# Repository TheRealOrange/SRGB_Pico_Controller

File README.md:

# RPi Pico Signal RGB Controller

This is a simple addressable RGB LED controller (WS2812 LEDs) based on the [Raspberry Pi Pico](https://www.raspberrypi.com/products/raspberry-pi-pico/), and compatible with the PC component RGB lighting software known as [Signal RGB](https://www.signalrgb.com/).  This controller features 8 independent addressable RGB LED outputs, each with filtering capacitors and a resistor on the data line per the recommended specifications. Each LED channel is also driven by the Pico through a level-shifter, providing full 5V to the data line. To supply 5V to the controller, there are two pads where the user can choose to solder a Molex, SATA power, or other 5V power source.

In case anyone wants to use this design, the KiCAD project files are in the folder `srgb_pico`, and the symbol fields list both LCSC and DigiKey part numbers.

The number of LEDs on each channel is configurable via the online configurator available at [SRGBmods](https://srgbmods.net/). The controller made possible by, and relies on the code provided by [SRGBmods](https://srgbmods.net/). I am not the author of the code which is meant to run on this controller.

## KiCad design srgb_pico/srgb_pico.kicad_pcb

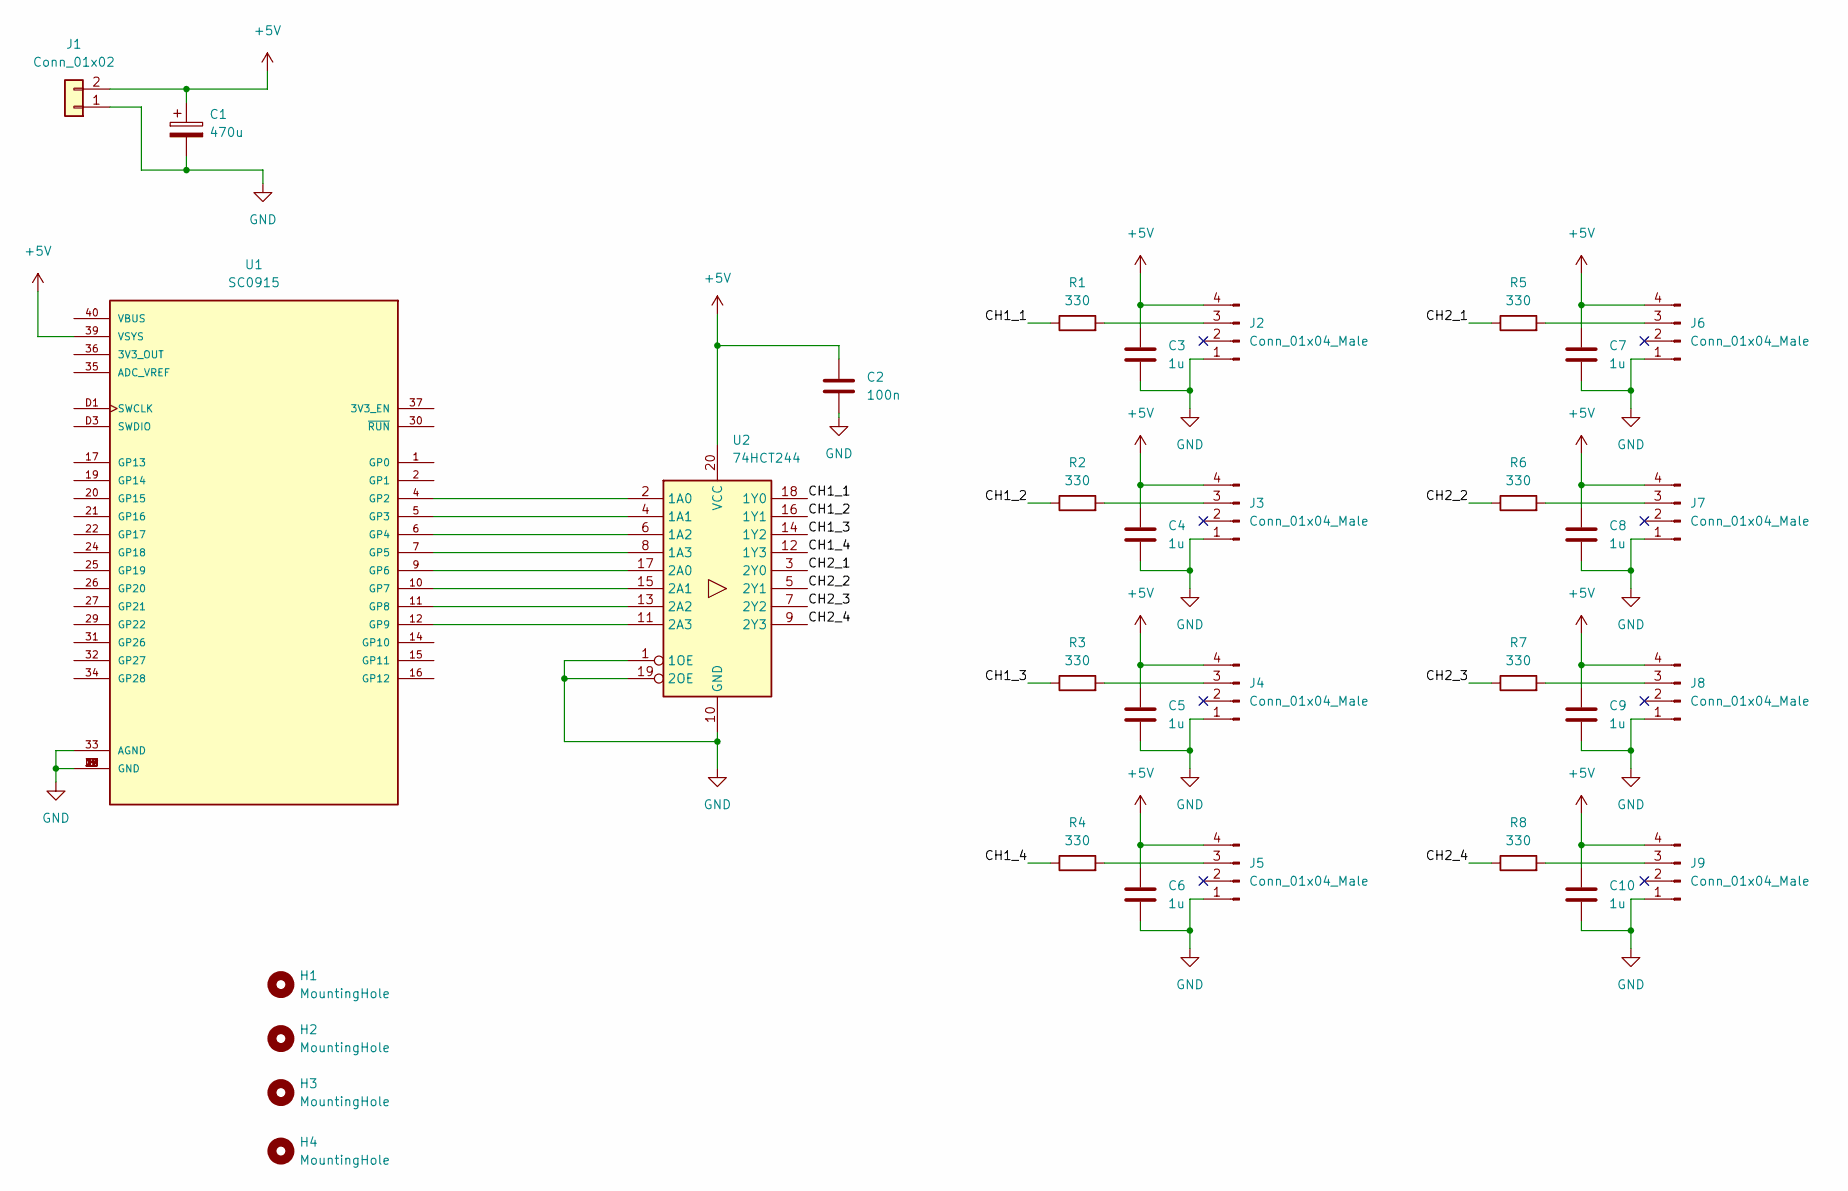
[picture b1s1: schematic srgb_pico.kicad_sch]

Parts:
C1: 470u; C_Elec_8x6.2; digikey_part_num 732-6451-1-ND
C2: 100n; C_0603_1608Metric; digikey_part_num 1276-1935-1-ND
C3, C4, C5, C6, C7, C8, C9, C10: 1u; C_0603_1608Metric; digikey_part_num 1276-1102-1-ND
H1, H2, H3, H4: MountingHole; MountingHole_3.2mm_M3_DIN965
J1: Conn_01x02; pwr_in
J2, J3, J4, J5, J6, J7, J8, J9: Conn_01x04_Male; PinHeader_ARGB_1x04_P2.54mm_Horizontal; digikey_part_num ED8564-04-ND
R1, R2, R3, R4, R5, R6, R7, R8: 330; R_0805_2012Metric; digikey_part_num A130131CT-ND
U1: SC0915; MODULE_SC0915; digikey_part_num 2648-SC0915CT-ND
U2: 74HCT244; SOIC-20W_7.5x12.8mm_P1.27mm; digikey_part_num 74HCT244DCT-ND

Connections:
+5V: C1.1, C2.2, C3.1, C4.1, C5.1, C6.1, C7.1, C8.1, C9.1, C10.1, J1.2, J2.4, J3.4, J4.4, J5.4, J6.4, J7.4, J8.4, J9.4, U1.39 (VSYS), U2.20 (VCC)
/CH1_1: R1.1, U2.18 (1Y0)
/CH1_2: R2.1, U2.16 (1Y1)
/CH1_3: R3.1, U2.14 (1Y2)
/CH1_4: R4.1, U2.12 (1Y3)
/CH2_1: R5.1, U2.3 (2Y0)
/CH2_2: R6.1, U2.5 (2Y1)
/CH2_3: R7.1, U2.7 (2Y2)
/CH2_4: R8.1, U2.9 (2Y3)
GND: C1.2, C2.1, C3.2, C4.2, C5.2, C6.2, C7.2, C8.2, C9.2, C10.2, J1.1, J2.1, J3.1, J4.1, J5.1, J6.1, J7.1, J8.1, J9.1, U1.3 (GND), U1.8 (GND), U1.13 (GND), U1.18 (GND), U1.23 (GND), U1.28 (GND), U1.33 (AGND), U1.38 (GND), U1.D2 (GND), U2.1 (1OE), U2.10 (GND), U2.19 (2OE)
unnamed: J2.3, R1.2
unnamed: J3.3, R2.2
unnamed: J4.3, R3.2
unnamed: J5.3, R4.2
unnamed: J6.3, R5.2
unnamed: J7.3, R6.2
unnamed: J8.3, R7.2
unnamed: J9.3, R8.2
unnamed: U1.4 (GP2), U2.2 (1A0)
unnamed: U1.5 (GP3), U2.4 (1A1)
unnamed: U1.6 (GP4), U2.6 (1A2)
unnamed: U1.7 (GP5), U2.8 (1A3)
unnamed: U1.9 (GP6), U2.17 (2A0)
unnamed: U1.10 (GP7), U2.15 (2A1)
unnamed: U1.11 (GP8), U2.13 (2A2)
unnamed: U1.12 (GP9), U2.11 (2A3)

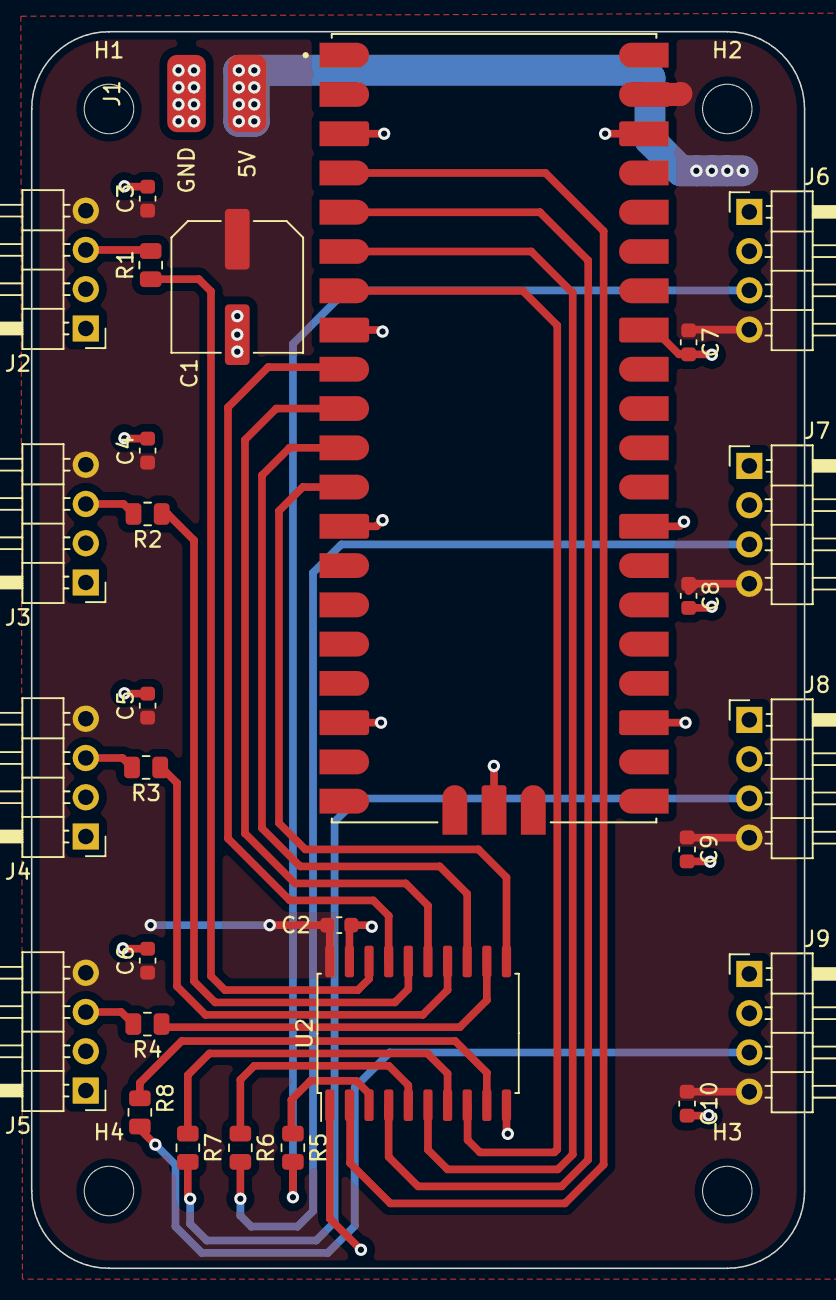
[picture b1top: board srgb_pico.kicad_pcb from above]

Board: 2 copper layers, 50.0 x 80.0 mm, 33 parts (0 on the bottom side), 26 nets.

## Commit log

2022-07-07 added kicad files
